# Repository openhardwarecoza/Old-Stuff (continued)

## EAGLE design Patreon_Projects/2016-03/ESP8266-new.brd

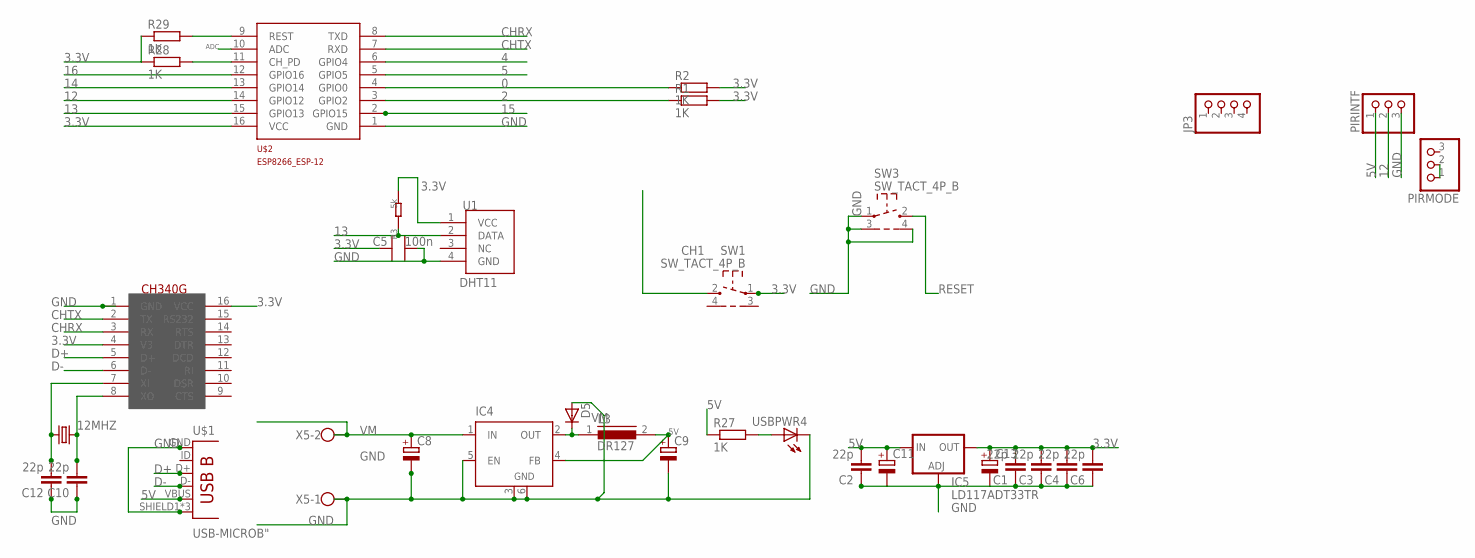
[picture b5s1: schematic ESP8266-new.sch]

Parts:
12MHZ: CRYSTALHC49UP; HC49UP
C1, C2, C3, C4, C6, C10, C12: 22p; C1206
C5: 100n; 0603
C8, C9: CPOL-EUE2.5-7; E2,5-7
C11, C13: CPOL-EUC; PANASONIC_C
D5: D-SOD-87; SOD87
IC4: LM2596S; TO263-5
IC5: LD117ADT33TR; DPACK
JP3: PINHD-1X4/90; 1X04/90
L3: DR127
PIRINTF: PINHD-1X3; 1X03
PIRMODE: PINHD-1X3; 1X03
R1, R2, R27, R28, R29: 1K; M1206
R3: 5k; 0603
SW1, SW3: SW_TACT_4P_B; SW_TACT_STANDARD_RIGHT_ANGLE
U1: DHT11
U$1: USB-MICROB"; USB-B-MICRO-SMD_V03
U$2: ESP8266_ESP-12; ESP8266-ESP12
U$4: CH340G; SOIC16
USBPWR4: LEDCHIP-LED0805; CHIP-LED0805
X5: W237-102

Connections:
0: R2.1, SW1.2, U$2.4 (GPIO0)
2: R1.1, U$2.3 (GPIO2)
3.3V: C1.2, C3.2, C4.2, C5.1, C6.2, C13.+, IC5.4 (OUT), R1.2, R2.2, R3.2, R28.1, R29.1, SW1.1, U1.1 (VCC), U$2.16 (VCC), U$4.4 (V3), U$4.16 (VCC)
4: U$2.6 (GPIO4)
5: U$2.5 (GPIO5)
5V: C2.2, C9.+, C11.+, IC4.4 (FB), IC5.3 (IN), L3.2, PIRINTF.1, R27.1, U$1.VBUS
12: PIRINTF.2, U$2.14 (GPIO12)
13: R3.1, U1.2 (DATA), U$2.15 (GPIO13)
14: U$2.13 (GPIO14)
15: U$2.2 (GPIO15)
16: U$2.12 (GPIO16)
ADC: U$2.10 (ADC)
CHRX: U$2.8 (TXD), U$4.3 (RX)
CHTX: U$2.7 (RXD), U$4.2 (TX)
D+: U$1.D+, U$4.5 (D+)
D-: U$1.D-, U$4.6 (D-)
GND: C1.1, C2.1, C3.1, C4.1, C5.2, C6.1, C8.-, C9.-, C10.1, C11.-, C12.1, C13.-, D5.2 (A), IC4.3 (GND), IC4.5 (EN), IC4.6 (GND), IC5.1 (ADJ), PIRINTF.3, SW3.1, SW3.3, SW3.4, U1.4 (GND), U$1.GND, U$1.SHIELD1 (SHIELD), U$1.SHIELD2 (SHIELD), U$1.SHIELD3 (SHIELD), U$2.1 (GND), U$4.1 (GND), USBPWR4.C, X5.1
unnamed: D5.1 (C), IC4.2 (OUT), L3.1
unnamed: R27.2, USBPWR4.A
unnamed: PIRMODE.1, PIRMODE.2
unnamed: 12MHZ.1, C12.2, U$4.7 (XI)
unnamed: 12MHZ.2, C10.2, U$4.8 (XO)
unnamed: R28.2, U$2.11 (CH_PD)
RESET: R29.2, SW3.2, U$2.9 (REST)
VM: C8.+, IC4.1 (IN), X5.2

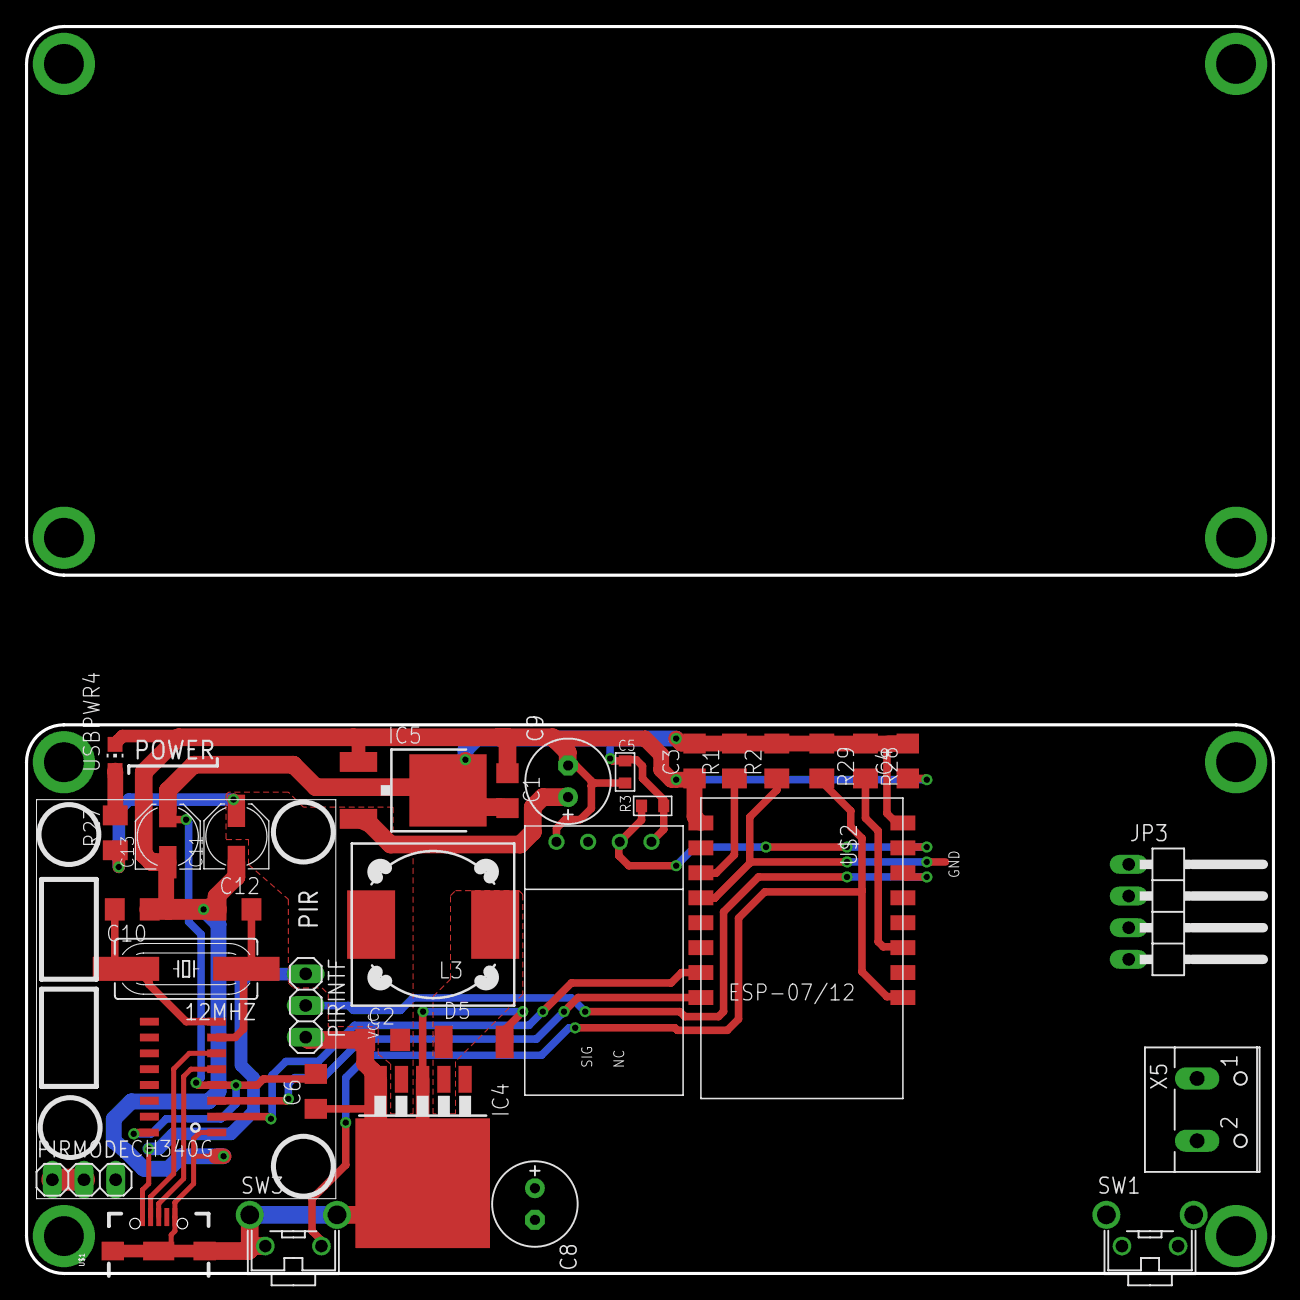
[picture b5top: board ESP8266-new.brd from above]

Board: 2 copper layers, 100.0 x 44.0 mm, 34 parts (0 on the bottom side), 19 nets.

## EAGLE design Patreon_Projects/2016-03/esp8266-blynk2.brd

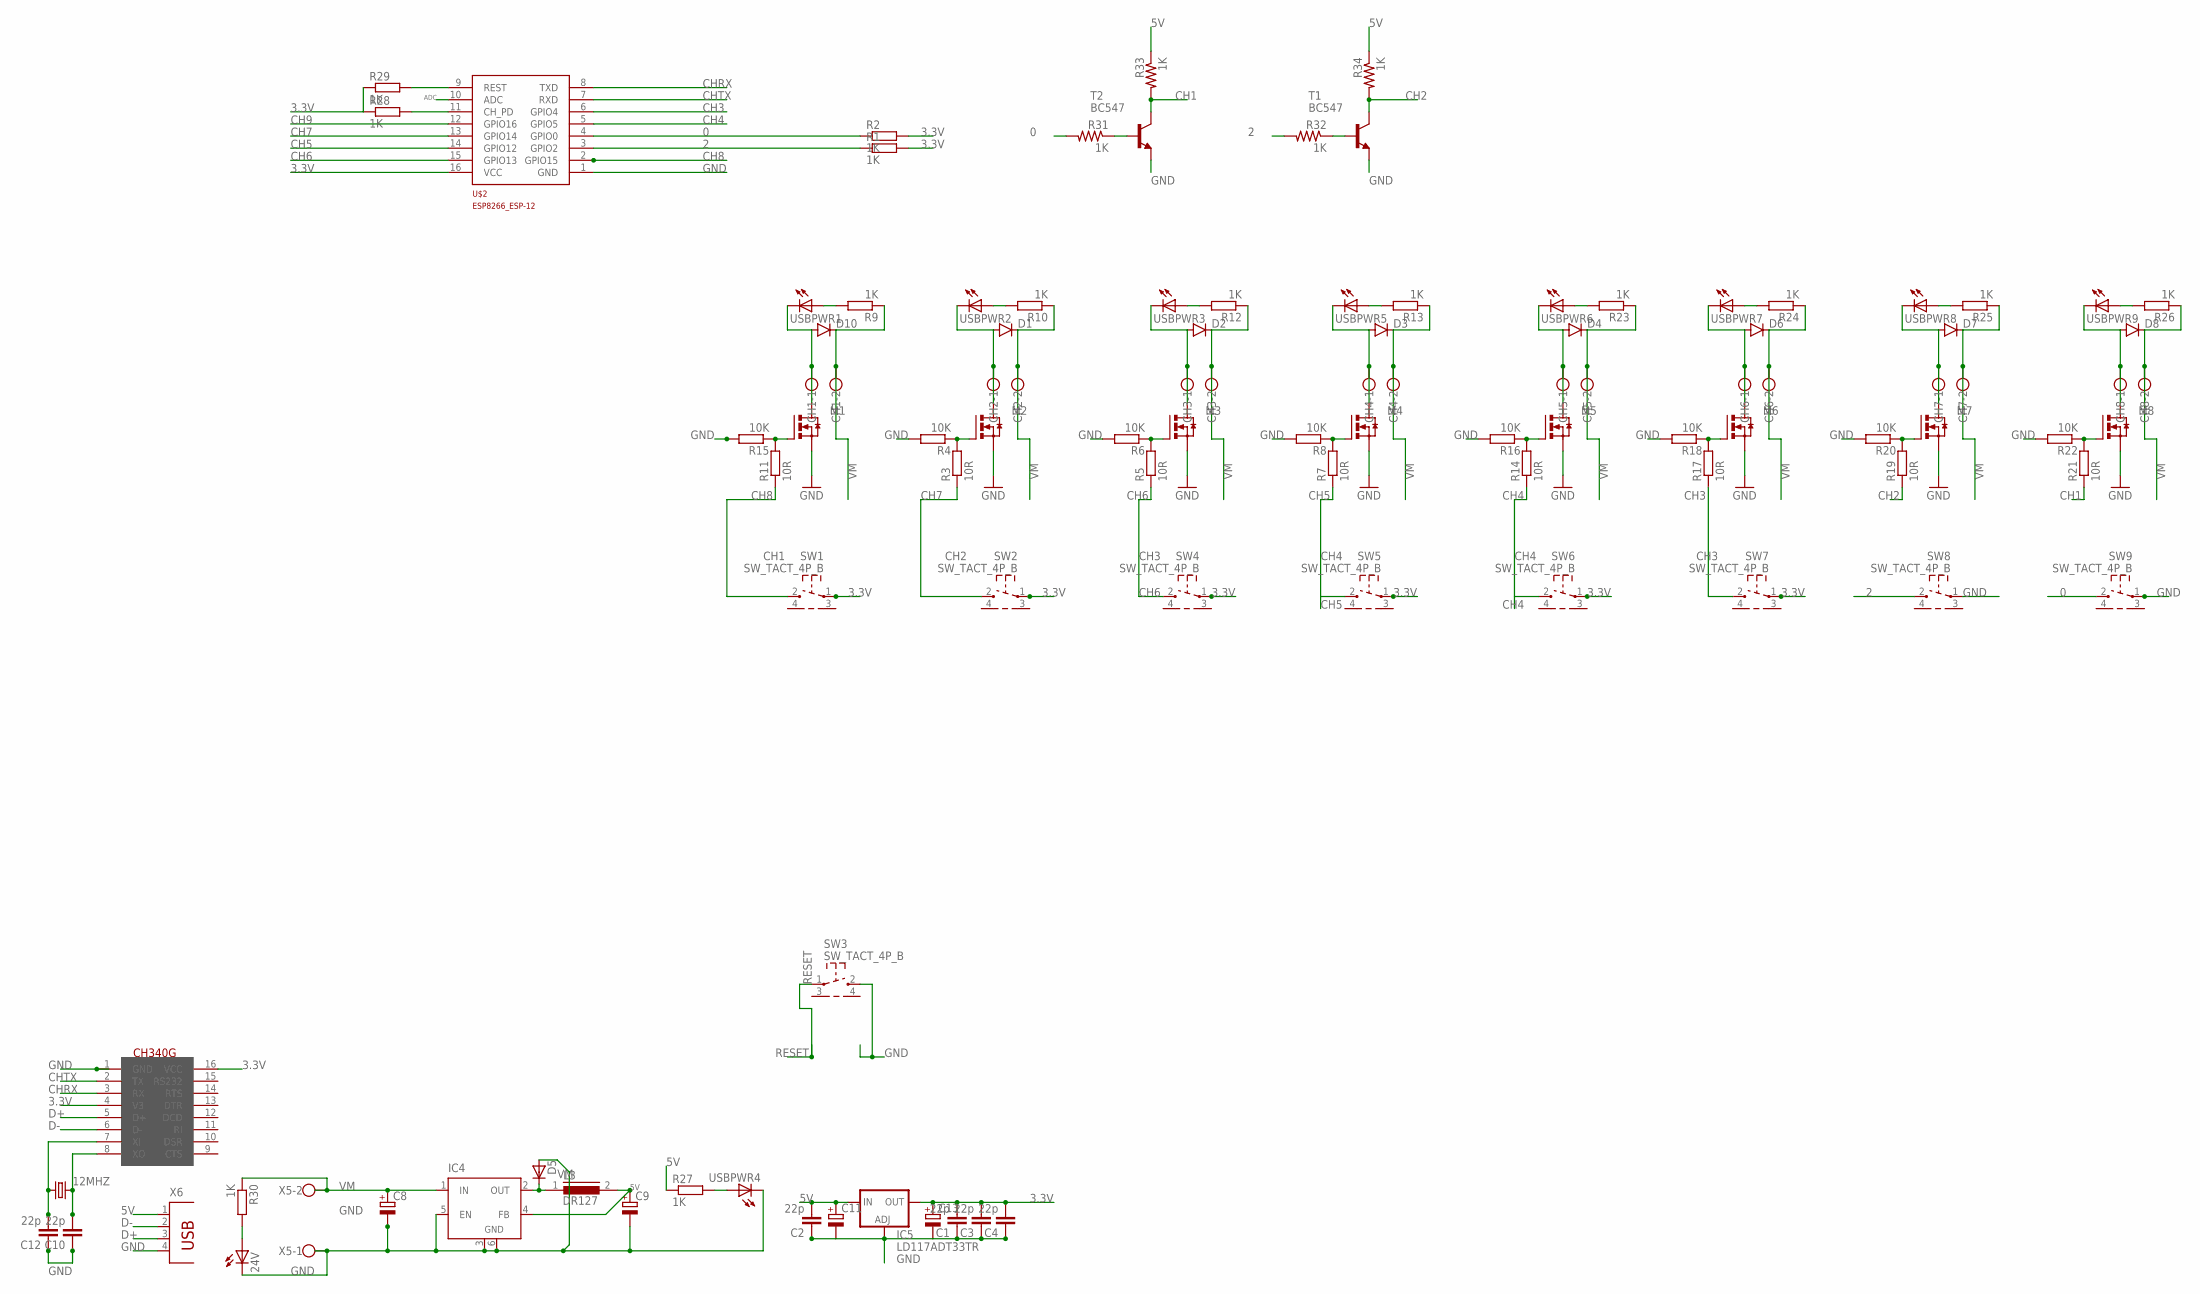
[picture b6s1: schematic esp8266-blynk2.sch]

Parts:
12MHZ: CRYSTALHC49UP; HC49UP
24V: LED3MM
C1, C2, C3, C4, C10, C12: 22p; C1206
C8, C9: CPOL-EUE2.5-7; E2,5-7
C11, C13: CPOL-EUC; PANASONIC_C
CH1, CH2, CH3, CH4, CH5, CH6, CH7, CH8: W237-102
D1, D2, D3, D4, D6, D7, D8, D10: DIODESMA-ALT; SMA-DIODE_ALT
D5: D-SOD-87; SOD87
IC4: LM2596S; TO263-5
IC5: LD117ADT33TR; DPACK
L3: DR127
M1, M2, M3, M4, M5, M6, M7, M8: IRLR024N; TO252
R1, R2, R9, R10, R12, R13, R23, R24, R25, R26, R27, R28, R29, R30, R31, R32, R33, R34: 1K; M1206
R3, R5, R7, R11, R14, R17, R19, R21: 10R; M1206
R4, R6, R8, R15, R16, R18, R20, R22: 10K; M1206
SW1, SW2, SW3, SW4, SW5, SW6, SW7, SW8, SW9: SW_TACT_4P_B; SW_TACT_STANDARD_RIGHT_ANGLE
T1, T2: BC547; TO92
U$2: ESP8266_ESP-12; ESP8266-ESP12
U$4: CH340G; SOIC16
USBPWR1, USBPWR2, USBPWR3, USBPWR4, USBPWR5, USBPWR6, USBPWR7, USBPWR8, USBPWR9: LED3MM
X5: W237-102
X6: PN61729

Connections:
0: R2.1, R31.2, SW9.2, U$2.4 (GPIO0)
2: R1.1, R32.2, SW8.2, U$2.3 (GPIO2)
3.3V: C1.2, C3.2, C4.2, C13.+, IC5.4 (OUT), R1.2, R2.2, R28.1, R29.1, SW1.1, SW2.1, SW4.1, SW5.1, SW6.1, SW7.1, U$2.16 (VCC), U$4.4 (V3), U$4.16 (VCC)
5V: C2.2, C9.+, C11.+, IC4.4 (FB), IC5.3 (IN), L3.2, R27.1, R33.1, R34.1, X6.1
ADC: U$2.10 (ADC)
CH1: R21.1, R33.2, T2.3 (C)
CH2: R19.1, R34.2, T1.3 (C)
CH3: R17.1, SW7.2, U$2.6 (GPIO4)
CH4: R14.1, SW6.2, U$2.5 (GPIO5)
CH5: R7.1, SW5.2, U$2.14 (GPIO12)
CH6: R5.1, SW4.2, U$2.15 (GPIO13)
CH7: R3.1, SW2.2, U$2.13 (GPIO14)
CH8: R11.1, SW1.2, U$2.2 (GPIO15)
CH9: U$2.12 (GPIO16)
CHRX: U$2.8 (TXD), U$4.3 (RX)
CHTX: U$2.7 (RXD), U$4.2 (TX)
D+: U$4.5 (D+), X6.3
D-: U$4.6 (D-), X6.2
GND: 24V.K (C), C1.1, C2.1, C3.1, C4.1, C8.-, C9.-, C10.1, C11.-, C12.1, C13.-, D5.2 (A), IC4.3 (GND), IC4.5 (EN), IC4.6 (GND), IC5.1 (ADJ), M1.2 (S), M2.2 (S), M3.2 (S), M4.2 (S), M5.2 (S), M6.2 (S), M7.2 (S), M8.2 (S), R4.2, R6.2, R8.2, R15.2, R16.2, R18.2, R20.2, R22.2, SW3.2, SW8.1, SW9.1, T1.1 (E), T2.1 (E), U$2.1 (GND), U$4.1 (GND), USBPWR4.K (C), X5.1, X6.4
unnamed: M2.1 (G), R3.2, R4.1
unnamed: M3.1 (G), R5.2, R6.1
unnamed: M4.1 (G), R7.2, R8.1
unnamed: R9.2, USBPWR1.A
unnamed: 24V.A, R30.2
unnamed: R10.2, USBPWR2.A
unnamed: R12.2, USBPWR3.A
unnamed: R13.2, USBPWR5.A
unnamed: D5.1 (C), IC4.2 (OUT), L3.1
unnamed: R27.2, USBPWR4.A
unnamed: 12MHZ.1, C12.2, U$4.7 (XI)
unnamed: 12MHZ.2, C10.2, U$4.8 (XO)
unnamed: R31.1, T2.2 (B)
unnamed: M5.1 (G), R14.2, R16.1
unnamed: R32.1, T1.2 (B)
unnamed: R28.2, U$2.11 (CH_PD)
unnamed: M6.1 (G), R17.2, R18.1
unnamed: M7.1 (G), R19.2, R20.1
unnamed: M8.1 (G), R21.2, R22.1
unnamed: R23.2, USBPWR6.A
unnamed: R24.2, USBPWR7.A
unnamed: R25.2, USBPWR8.A
unnamed: R26.2, USBPWR9.A
unnamed: M1.1 (G), R11.2, R15.1
OUT1: CH1.1, D10.A, M1.3 (D), USBPWR1.K (C)
OUT2: CH2.1, D1.A, M2.3 (D), USBPWR2.K (C)
OUT3: CH3.1, D2.A, M3.3 (D), USBPWR3.K (C)
OUT4: CH4.1, D3.A, M4.3 (D), USBPWR5.K (C)
OUT5: CH5.1, D4.A, M5.3 (D), USBPWR6.K (C)
OUT6: CH6.1, D6.A, M6.3 (D), USBPWR7.K (C)
OUT7: CH7.1, D7.A, M7.3 (D), USBPWR8.K (C)
OUT8: CH8.1, D8.A, M8.3 (D), USBPWR9.K (C)
RESET: R29.2, SW3.1, U$2.9 (REST)
VM: C8.+, CH1.2, CH2.2, CH3.2, CH4.2, CH5.2, CH6.2, CH7.2, CH8.2, D1.C, D2.C, D3.C, D4.C, D6.C, D7.C, D8.C, D10.C, IC4.1 (IN), R9.1, R10.1, R12.1, R13.1, R23.1, R24.1, R25.1, R26.1, R30.1, X5.2

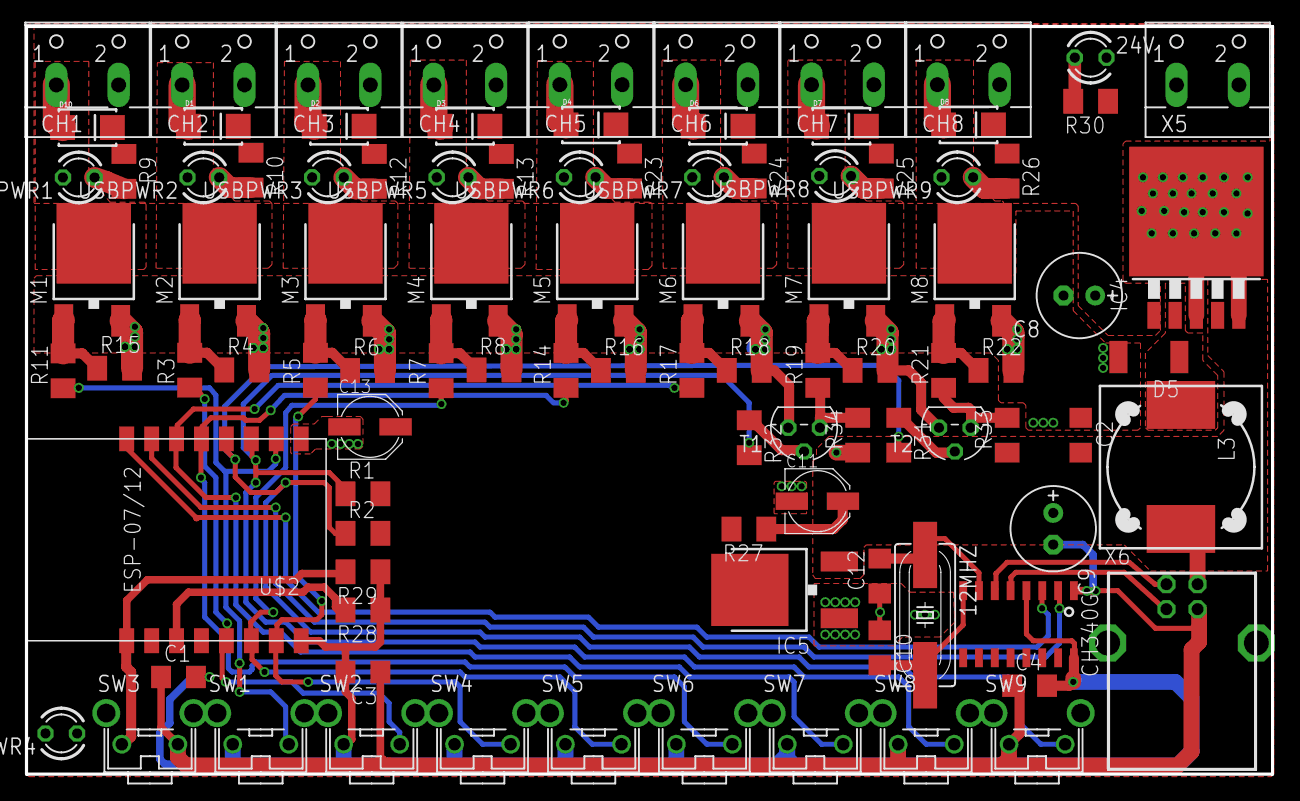
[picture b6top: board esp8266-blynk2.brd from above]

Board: 2 copper layers, 100.0 x 60.0 mm, 98 parts (0 on the bottom side), 51 nets.

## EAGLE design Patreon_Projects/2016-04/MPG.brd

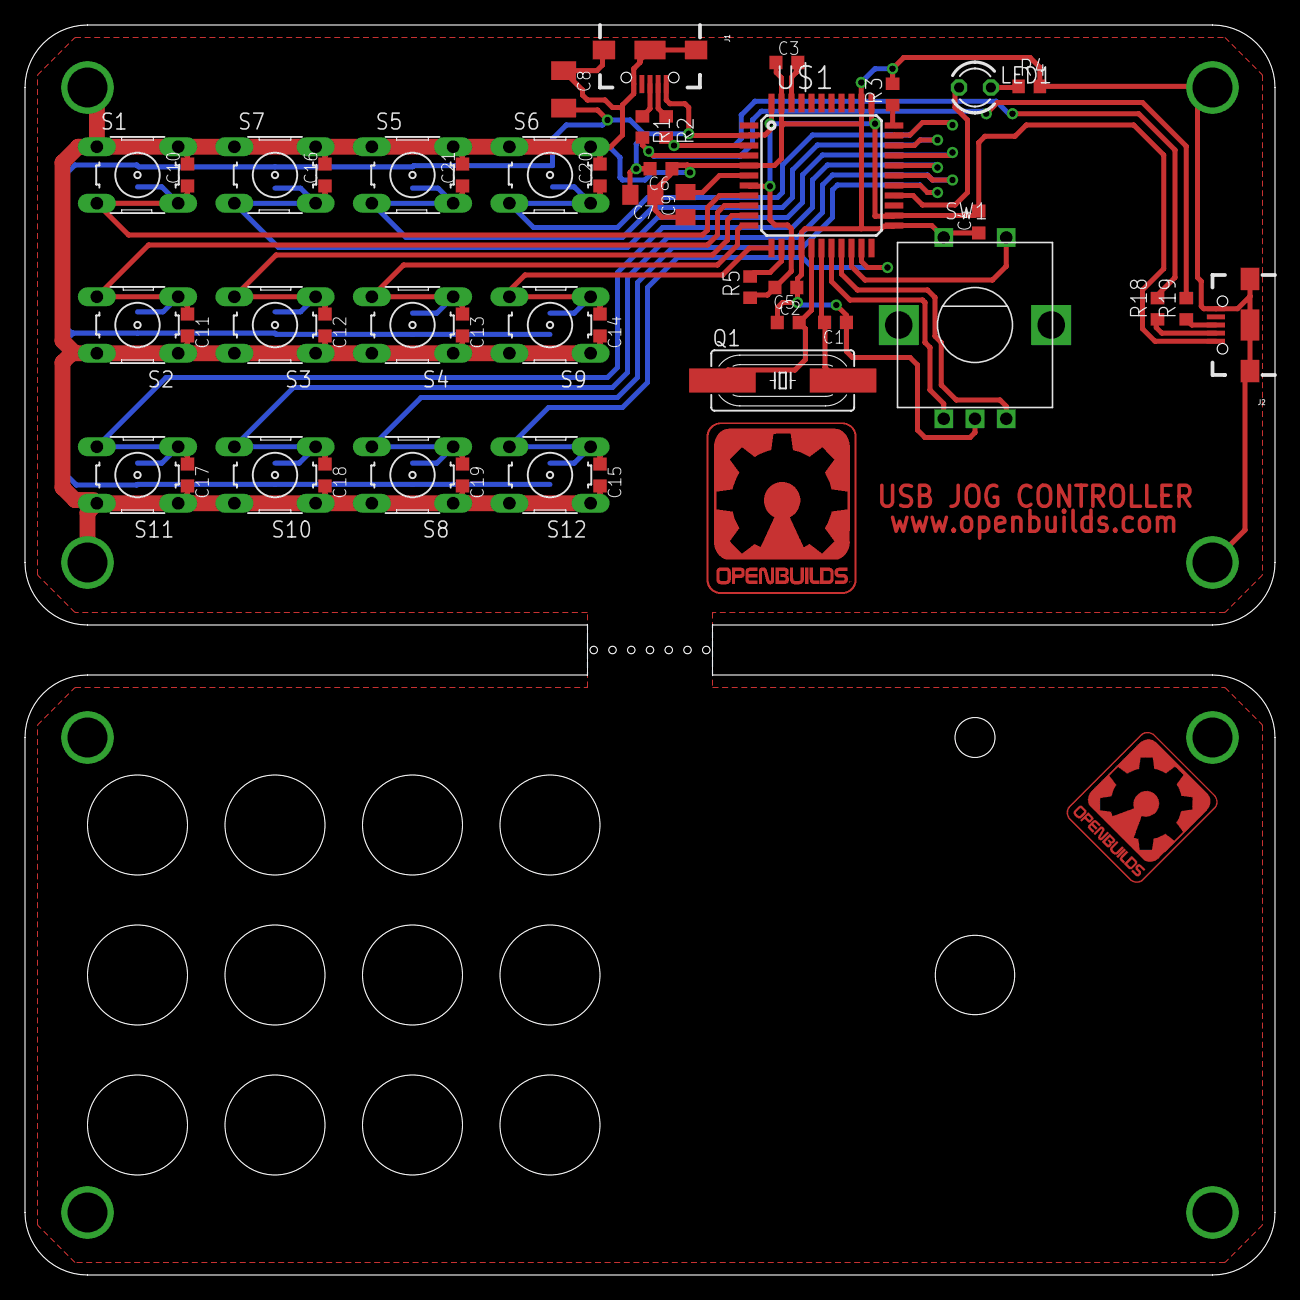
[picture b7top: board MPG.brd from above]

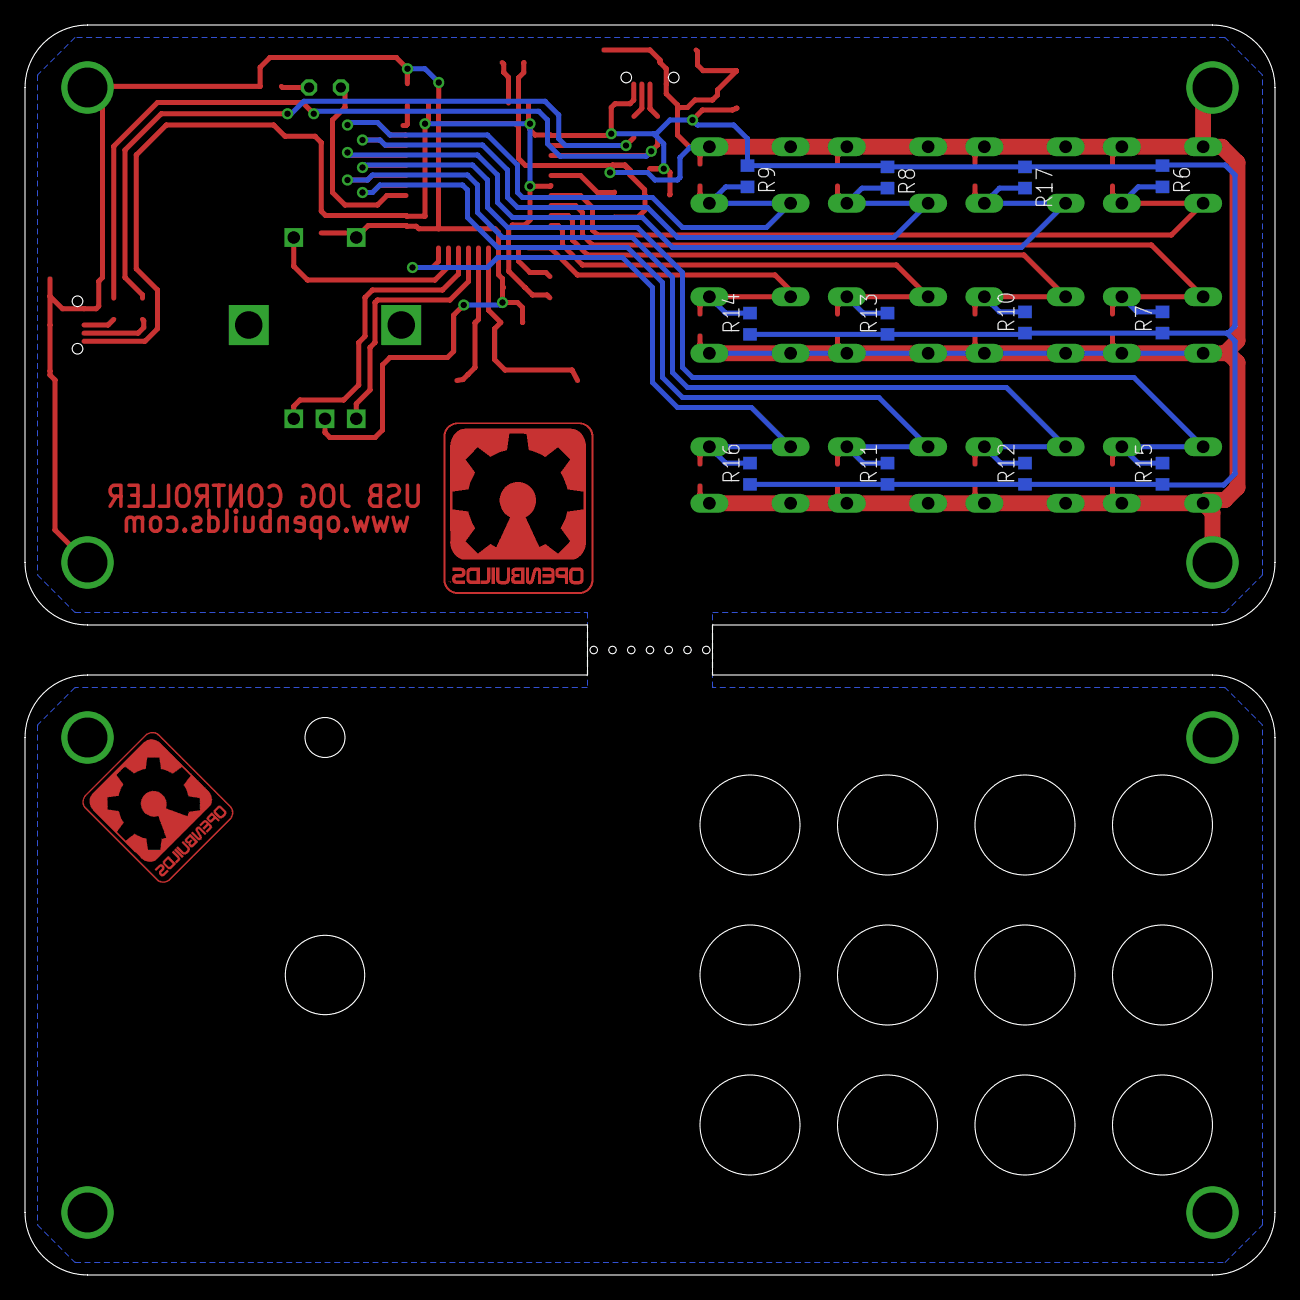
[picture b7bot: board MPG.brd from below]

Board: 2 copper layers, 100.0 x 100.0 mm, 58 parts (12 on the bottom side), 31 nets.

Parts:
C1, C2, C3, C4, C5, C6, C10, C11, C12, C13, C14, C15, C16, C17, C18, C19, C20, C21: C0603K
C7, C9: C0805K
C8: C1206K
J1, J2: USB-B-MICRO-SMD_V03
LED1: LED3MM
Q1: HC49UP
R1, R2, R3, R4, R5, R6, R7, R8, R9, R10, R11, R12, R13, R14, R15, R16, R17, R18, R19: R0603
S1, S2, S3, S4, S5, S6, S7, S8, S9, S10, S11, S12: B3F-10XX
SW1: EC12E_SW; ALPS_EC12E_SW
U$1: ATMEGA32U4-AU; TQFP44

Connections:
D0: C10.1, R6.2, S1.3, S1.4, U$1.8
D1: C11.1, R7.2, S2.3, S2.4, U$1.9
D2: C12.1, R10.2, S3.3, S3.4, U$1.10
D3: C13.1, R13.2, S4.3, S4.4, U$1.11
D4PWM: C14.1, R14.2, S9.3, S9.4, U$1.12
D5PWM: SW1.A, U$1.18
D6: SW1.B, U$1.19
D7: SW1.E, U$1.20
D8: C15.1, R16.2, S12.3, S12.4, U$1.21
D9PWM: C21.1, R8.2, S5.3, S5.4, U$1.31
D10PWM: C20.1, R9.2, S6.3, S6.4, U$1.32
D11: LED1.A, U$1.26
D12: C19.1, R11.2, S8.3, S8.4, U$1.27
D13: C18.1, R12.2, S10.3, S10.4, U$1.28
D14: C17.1, R15.2, S11.3, S11.4, U$1.29
D15: C16.1, R17.2, S7.3, S7.4, U$1.30
GND: C1.1, C2.1, C3.1, C4.1, C5.1, C6.1, C7.1, C8.1, C9.1, C10.2, C11.2, C12.2, C13.2, C14.2, C15.2, C16.2, C17.2, C18.2, C19.2, C20.2, C21.2, J1.GND, J1.SHIELD1, J1.SHIELD2, J1.SHIELD3, J2.GND, J2.SHIELD1, J2.SHIELD2, J2.SHIELD3, R3.2, R4.2, S1.1, S1.2, S2.1, S2.2, S3.1, S3.2, S4.1, S4.2, S5.1, S5.2, S6.1, S6.2, S7.1, S7.2, S8.1, S8.2, S9.1, S9.2, S10.1, S10.2, S11.1, S11.2, S12.1, S12.2, SW1.C, SW1.D, U$1.5, U$1.15, U$1.23, U$1.35, U$1.43
unnamed: R1.2, R19.2, U$1.4
unnamed: R2.2, R18.2, U$1.3
unnamed: R3.1, U$1.33
unnamed: C2.2, Q1.1, U$1.16
unnamed: C1.2, Q1.2, U$1.17
unnamed: R5.2, U$1.13
unnamed: C3.2, U$1.42
unnamed: C9.2, U$1.6
unnamed: LED1.K, R4.1
USBD+L: J2.D+, R19.1
USBD+T: J1.D+, R1.1
USBD-L: J2.D-, R18.1
USBD-T: J1.D-, R2.1
VCC: C4.2, C5.2, C6.2, C7.2, C8.2, J1.VBUS, J2.VBUS, R5.1, R6.1, R7.1, R8.1, R9.1, R10.1, R11.1, R12.1, R13.1, R14.1, R15.1, R16.1, R17.1, U$1.2, U$1.7, U$1.14, U$1.24, U$1.34, U$1.44

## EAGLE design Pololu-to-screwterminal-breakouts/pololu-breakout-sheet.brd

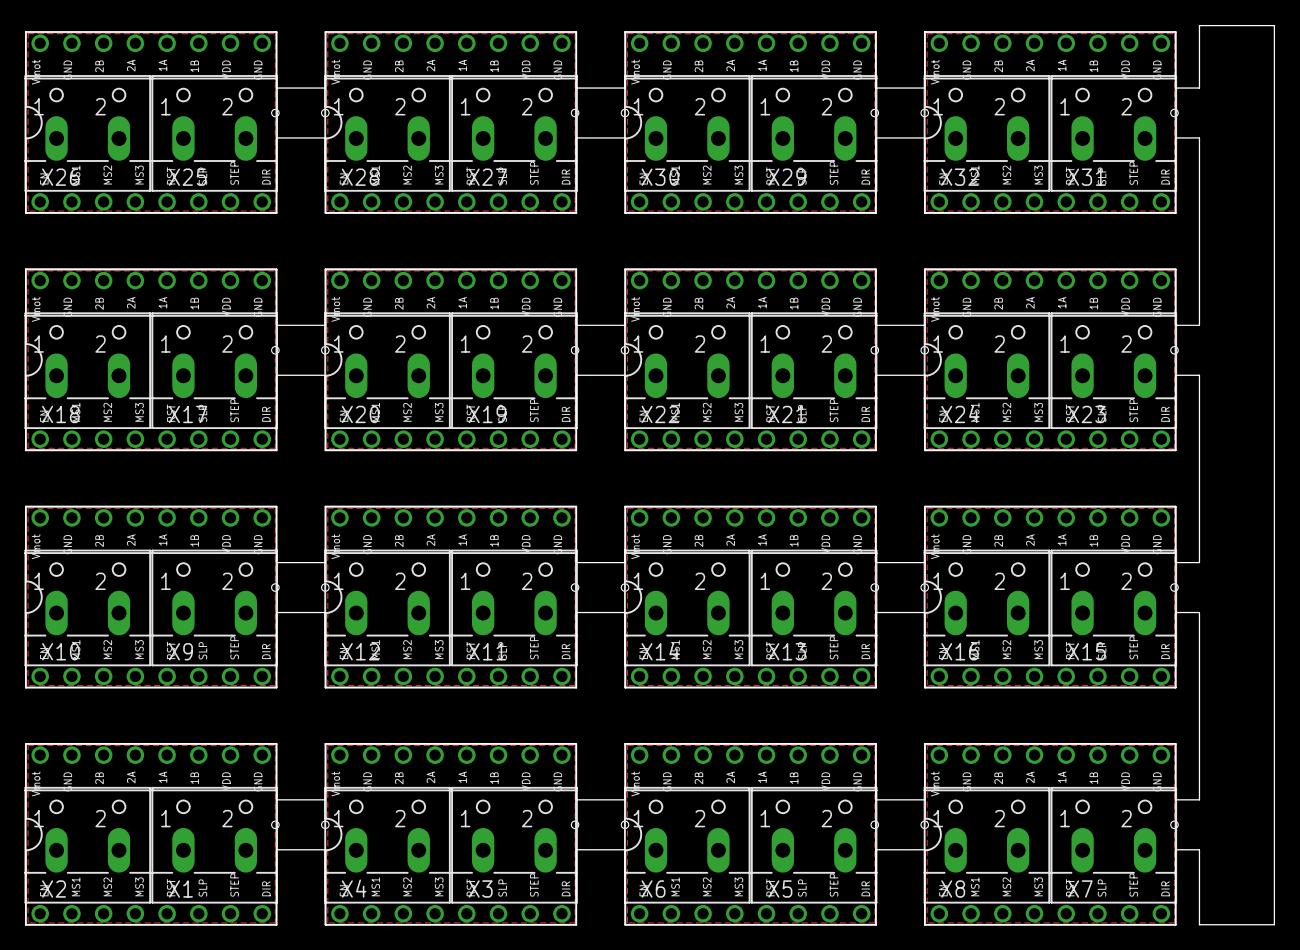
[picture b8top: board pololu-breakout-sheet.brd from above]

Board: 2 copper layers, 100.0 x 72.0 mm, 48 parts (0 on the bottom side), 64 nets, no tracks yet.

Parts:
U$1, U$2, U$3, U$4, U$5, U$6, U$7, U$8, U$9, U$10, U$11, U$12, U$13, U$14, U$15, U$16: POLOLU_A4983CARRIER; A4988BREAKOUT
X1, X2, X3, X4, X5, X6, X7, X8, X9, X10, X11, X12, X13, X14, X15, X16, X17, X18, X19, X20, X21, X22, X23, X24, X25, X26, X27, X28, X29, X30, X31, X32: W237-102

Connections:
unnamed: U$1.EN, X2.1
unnamed: U$1.STEP, X2.2
unnamed: U$1.DIR, X1.1
unnamed: U$1.GND, U$1.GND@0, X1.2
unnamed: U$2.EN, X4.1
unnamed: U$2.STEP, X4.2
unnamed: U$2.DIR, X3.1
unnamed: U$2.GND, U$2.GND@0, X3.2
unnamed: U$3.EN, X6.1
unnamed: U$3.STEP, X6.2
unnamed: U$3.DIR, X5.1
unnamed: U$3.GND, U$3.GND@0, X5.2
unnamed: U$4.EN, X8.1
unnamed: U$4.STEP, X8.2
unnamed: U$4.DIR, X7.1
unnamed: U$4.GND, U$4.GND@0, X7.2
unnamed: U$5.EN, X10.1
unnamed: U$5.STEP, X10.2
unnamed: U$5.DIR, X9.1
unnamed: U$5.GND, U$5.GND@0, X9.2
unnamed: U$6.EN, X12.1
unnamed: U$6.STEP, X12.2
unnamed: U$6.DIR, X11.1
unnamed: U$6.GND, U$6.GND@0, X11.2
unnamed: U$7.EN, X14.1
unnamed: U$7.STEP, X14.2
unnamed: U$7.DIR, X13.1
unnamed: U$7.GND, U$7.GND@0, X13.2
unnamed: U$8.EN, X16.1
unnamed: U$8.STEP, X16.2
unnamed: U$8.DIR, X15.1
unnamed: U$8.GND, U$8.GND@0, X15.2
unnamed: U$9.EN, X18.1
unnamed: U$9.STEP, X18.2
unnamed: U$9.DIR, X17.1
unnamed: U$9.GND, U$9.GND@0, X17.2
unnamed: U$10.EN, X20.1
unnamed: U$10.STEP, X20.2
unnamed: U$10.DIR, X19.1
unnamed: U$10.GND, U$10.GND@0, X19.2
unnamed: U$11.EN, X22.1
unnamed: U$11.STEP, X22.2
unnamed: U$11.DIR, X21.1
unnamed: U$11.GND, U$11.GND@0, X21.2
unnamed: U$12.EN, X24.1
unnamed: U$12.STEP, X24.2
unnamed: U$12.DIR, X23.1
unnamed: U$12.GND, U$12.GND@0, X23.2
unnamed: U$13.EN, X26.1
unnamed: U$13.STEP, X26.2
unnamed: U$13.DIR, X25.1
unnamed: U$13.GND, U$13.GND@0, X25.2
unnamed: U$14.EN, X28.1
unnamed: U$14.STEP, X28.2
unnamed: U$14.DIR, X27.1
unnamed: U$14.GND, U$14.GND@0, X27.2
unnamed: U$15.EN, X30.1
unnamed: U$15.STEP, X30.2
unnamed: U$15.DIR, X29.1
unnamed: U$15.GND, U$15.GND@0, X29.2
unnamed: U$16.EN, X32.1
unnamed: U$16.STEP, X32.2
unnamed: U$16.DIR, X31.1
unnamed: U$16.GND, U$16.GND@0, X31.2
